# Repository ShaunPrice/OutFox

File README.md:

# OutFox
This is a volunteer project to help save the endangered Bell turtle species. I'm assisting the "Turtles Forever" project team in developing a fox (and dogs) detection and scaring system that uses Artificial Intelligence (AI) to identify the preditors and ward them off. The main preditor causing the damage has been foxes that are not native to Australia and are destroying the turtle nests.

This is the working prototype (PCB not validated) for the solution. It uses MobileNet AI model as it already detects many species of foxes, dogs and wolves.

*Any assistance in this project is welcome!!!*

## Articles About the Project
https://www.abc.net.au/news/2018-03-07/turtle-hatchlings-offer-hope-endangered-bells-turtle/9522182
https://northerntablelands.lls.nsw.gov.au/resource-hub/media-releases/2016/work-begins-on-bells-turtle-recovery-project

Fox and other nuisance animal detection and frightening device. Uses cameras and AI to detect and identify only the nuisance animals.

*This is a Work in Progress*
# Notes for using the Seeed Studio MAIX Bit and the Kendryte K210

## Sipeed MAix BiT for RISC-V AI+IoT
The core of the system is the Sipeed BiT board with camera available from Seeed. 
https://www.seeedstudio.com/Sipeed-MAix-BiT-for-RISC-V-AI-IoT-p-2872.html

This board uses a Kendryte K210 Neural Accellerator for at the edge AI. The board consumes less than 1 Watt of power.

If using this board and camera for night vision using the IR LEDs you'll need to unscrew the lense from the camera and remove the small square IR filter from the back of the lense.

The documentation for this processor is available here:
https://maixpy.sipeed.com/en/

## SiSpeed Downloads
http://dl.sipeed.com/MAIX/
https://github.com/sipeed

## Uploading files and firmware
Use uPyLoader for uploading files and executing script
Use kloader_windows for uploading firmware

The details of obtaining and using these tools is available from the Sipeed website:

https://maixpy.sipeed.com/en/get_started/upload_script.html

## MaixPy Firmware
Builds:   http://dl.sipeed.com/MAIX/MaixPy/release/master/
GitHub: https://github.com/sipeed/MaixPy/releases

## Train, Convert and Run Models for MaixPy 
The following article explains how to train, convert and run AI modules on the MAix BiT and other modules using the Kendryte K210 processor.
https://bbs.sipeed.com/t/topic/682

### Package Kfpkg files
http://blog.sipeed.com/p/390.html
**Note 1:** *SD library does not support long file names.*
**Note 2:** *name.kmodel files are in the zipped file name.kfpkg*

kfpkg files are zipped files containing the following files:

	model.kmodel file that is the inference model
	flash-list.json file that tells the loaded where to put the model in flash memory
	
A typical kfpkg flash-list.json file is below where facedetect.kmodel is the name of the kmodel file:
'''json
{
    "version": "0.1.0",
     "files": [
        {
            "address": 0x00300000,
            "bin": "facedetect.kmodel",
            "sha256Prefix": false
        }
    ]
}
'''

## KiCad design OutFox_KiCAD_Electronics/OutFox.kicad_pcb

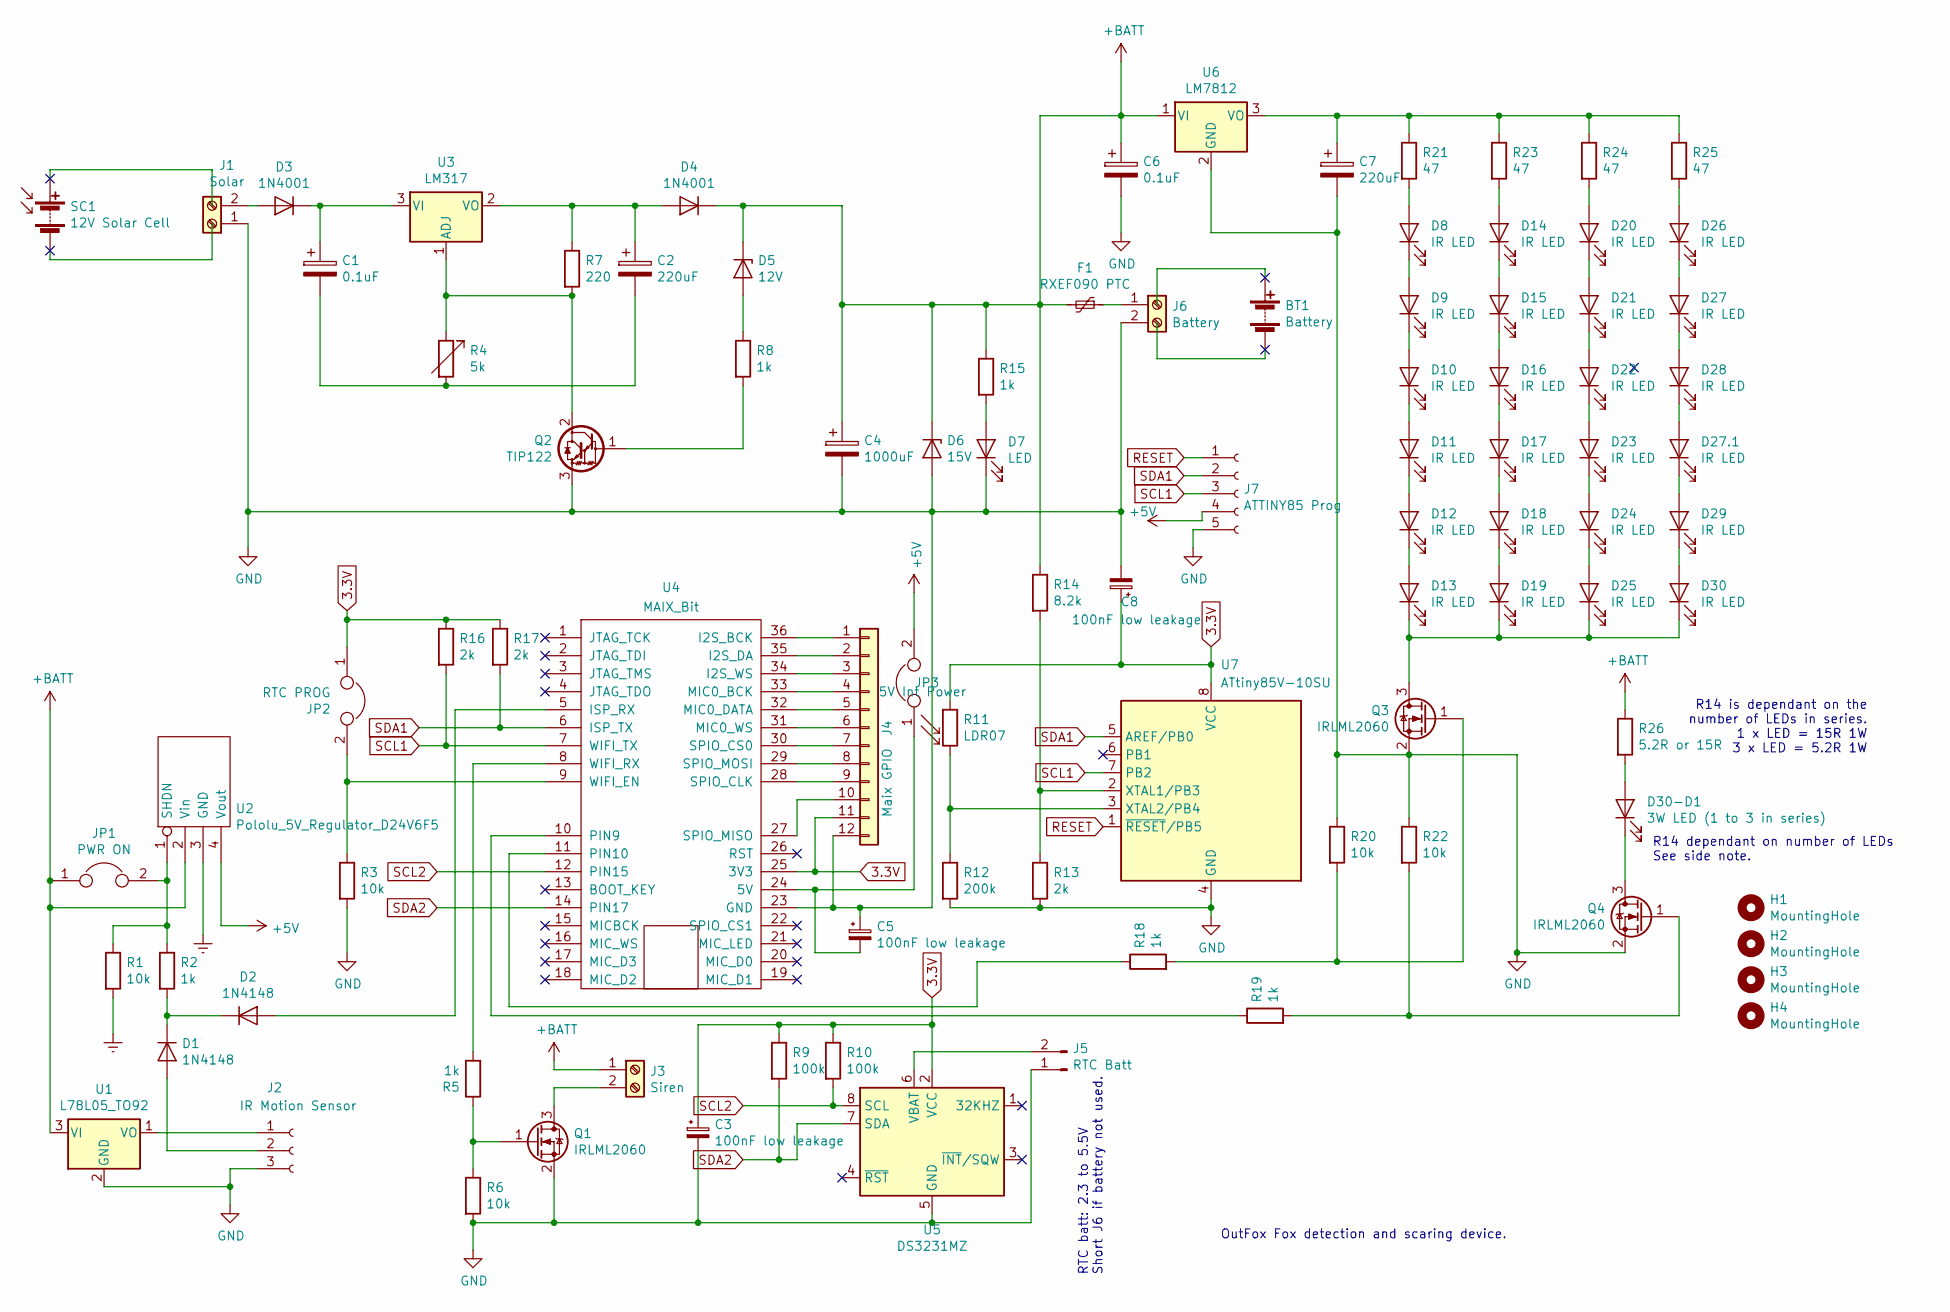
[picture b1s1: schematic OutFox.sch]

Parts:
BT1: Battery
C1, C6: 0.1uF; CP_Radial_D4.0mm_P1.50mm
C2, C7: 220uF; CP_Radial_D5.0mm_P2.50mm
C3, C5, C8: 100nF low leakage; C_0603_HandSoldering
C4: 1000uF; CP_Radial_D5.0mm_P2.50mm
D1, D2: 1N4148; D_A-405_P7.62mm_Horizontal
D3, D4: 1N4001; D_DO-15_P12.70mm_Horizontal
D5: 12V; D_DO-15_P12.70mm_Horizontal
D6: 15V; D_DO-15_P12.70mm_Horizontal
D7: LED; LED_D3.0mm
D8, D9, D10, D11, D12, D13, D14, D15, D16, D17, D18, D19, D20, D21, D22, D23, D24, D25, D26, D27, D27.1, D28, D29, D30: IR LED; LED_D5.0mm
D30-D1: 3W LED (1 to 3 in series); LED_D5.0mm
F1: RXEF090 PTC; Fuse_TE5_Littlefuse-395Series
H1, H2, H3, H4: MountingHole; MountingHole_3.2mm_M3
J1: Solar; TerminalBlock_bornier-2_P5.08mm
J2: IR Motion Sensor; Pin_Header_Straight_1x03_Pitch2.54mm
J3: Siren; TerminalBlock_bornier-2_P5.08mm
J4: Maix GPIO; Socket_Strip_Straight_1x12_Pitch2.54mm
J5: RTC Batt; JST_PH_B2B-PH-K_02x2.00mm_Straight
J6: Battery; TerminalBlock_bornier-2_P5.08mm
J7: ATTINY85 Prog; Pin_Header_Straight_1x05_Pitch2.54mm
JP1: PWR ON; Pin_Header_Straight_1x02_Pitch2.54mm
JP2: RTC PROG; Pin_Header_Straight_1x02_Pitch2.54mm
JP3: 5V Int Power; Pin_Header_Straight_1x02_Pitch2.54mm
Q1, Q3, Q4: IRLML2060; SOT-23
Q2: TIP122; TO-220-3_Vertical
R1, R3, R6, R20, R22: 10k; R_Axial_DIN0207_L6.3mm_D2.5mm_P10.16mm_Horizontal
R2, R5, R8, R15, R18, R19: 1k; R_Axial_DIN0207_L6.3mm_D2.5mm_P10.16mm_Horizontal
R4: 5k; Potentiometer_Trimmer_Bourns_3266Y
R7: 220; R_Axial_DIN0207_L6.3mm_D2.5mm_P10.16mm_Horizontal
R9, R10: 100k; R_0603_HandSoldering
R11: LDR07; R_Axial_DIN0204_L3.6mm_D1.6mm_P2.54mm_Vertical
R12: 200k; R_0603_HandSoldering
R13, R16, R17: 2k; R_0603_HandSoldering
R14: 8.2k; R_0603_HandSoldering
R21, R23, R24, R25: 47; R_Axial_DIN0207_L6.3mm_D2.5mm_P10.16mm_Horizontal
R26: 5.2R or 15R; R_Axial_DIN0207_L6.3mm_D2.5mm_P10.16mm_Horizontal
SC1: 12V Solar Cell
U1: L78L05_TO92; TO-92_Inline_Narrow_Oval
U2: Pololu_5V_Regulator_D24V6F5; Polulu_Voltage_Regulator
U3: LM317; TO-220
U4: MAIX_Bit; MAIXBit
U5: DS3231MZ; SOIC-8_3.9x4.9mm_Pitch1.27mm
U6: LM7812; TO-220-3_Vertical
U7: ATtiny85V-10SU; SOIC-8-N

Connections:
3.3V: C3.1, C8.1, J4.11, JP2.1, R9.1, R10.1, R11.1, R16.1, R17.1, U4.25 (3V3), U5.2 (VCC), U7.8 (VCC)
+5V: J7.4, JP3.2, U2.4 (Vout)
+BATT: C4.1, C6.1, D4.1 (K), D5.1 (K), D6.1 (K), F1.2, J3.1, JP1.1, R14.1, R15.1, R26.1, U1.3 (VI), U2.2 (Vin), U6.1 (VI)
Earth: R1.2, U2.3 (GND)
GND: C3.2, C4.2, C5.1, C6.2, C7.2, C8.2, D6.2 (A), D7.1 (K), J1.1, J2.3 (GND), J4.12, J5.1, J6.2, J7.5, Q1.2 (S), Q2.3 (E), Q3.2 (S), Q4.2 (S), R3.2, R6.2, R12.2, R13.2, R20.1, R22.1, U1.2 (GND), U4.23 (GND), U5.5 (GND), U6.2 (GND), U7.4 (GND)
unnamed: C1.1, D3.1 (K), U3.3 (VI)
unnamed: C1.2, C2.2, R4.2
unnamed: C2.1, D4.2 (A), R7.1, U3.2 (VO)
unnamed: C5.2, JP3.1, U4.24 (5V)
unnamed: C7.1, R21.1, R23.1, R24.1, R25.1, U6.3 (VO)
unnamed: D1.1 (K), D2.1 (K), R2.2
unnamed: D1.2 (A), J2.2 (OUT)
unnamed: D2.2 (A), U4.5 (ISP_RX)
unnamed: D3.2 (A), J1.2
unnamed: D5.2 (A), R8.1
unnamed: D7.2 (A), R15.2
unnamed: D8.1 (K), D9.2 (A)
unnamed: D8.2 (A), R21.2
unnamed: D10.1 (K), D11.2 (A)
unnamed: D9.1 (K), D10.2 (A)
unnamed: D11.1 (K), D12.2 (A)
unnamed: D12.1 (K), D13.2 (A)
unnamed: D13.1 (K), D19.1 (K), D25.1 (K), D30.1 (K), Q3.3 (D)
unnamed: D14.1 (K), D15.2 (A)
unnamed: D14.2 (A), R23.2
unnamed: D15.1 (K), D16.2 (A)
unnamed: D16.1 (K), D17.2 (A)
unnamed: D17.1 (K), D18.2 (A)
unnamed: D18.1 (K), D19.2 (A)
unnamed: D20.1 (K), D21.2 (A)
unnamed: D20.2 (A), R24.2
unnamed: D21.1 (K), D22.2 (A)
unnamed: D22.1 (K), D23.2 (A)
unnamed: D23.1 (K), D24.2 (A)
unnamed: D24.1 (K), D25.2 (A)
unnamed: D26.1 (K), D27.2 (A)
unnamed: D26.2 (A), R25.2
unnamed: D27.1 (K), D28.2 (A)
unnamed: D27.1.1 (K), D29.2 (A)
unnamed: D27.1.2 (A), D28.1 (K)
unnamed: D29.1 (K), D30.2 (A)
unnamed: D30-D1.1 (K), Q4.3 (D)
unnamed: D30-D1.2 (A), R26.2
unnamed: F1.1, J6.1
unnamed: J2.1 (5V), U1.1 (VO)
unnamed: J3.2, Q1.3 (D)
unnamed: J4.1, U4.36 (I2S_BCK)
unnamed: J4.2, U4.35 (I2S_DA)
unnamed: J4.3, U4.34 (I2S_WS)
unnamed: J4.4, U4.33 (MIC0_BCK)
unnamed: J4.5, U4.32 (MIC0_DATA)
unnamed: J4.6, U4.31 (MIC0_WS)
unnamed: J4.7, U4.30 (SPIO_CS0)
unnamed: J4.8, U4.29 (SPIO_MOSI)
unnamed: J4.9, U4.28 (SPIO_CLK)
unnamed: J4.10, U4.27 (SPIO_MISO)
unnamed: J5.2, U5.6 (VBAT)
unnamed: JP1.2, R1.1, R2.1, U2.1 (SHDN)
unnamed: JP2.2, R3.1, U4.9 (WIFI_EN)
unnamed: Q1.1 (G), R5.1, R6.1
unnamed: Q2.1 (B), R8.2
unnamed: Q2.2 (C), R4.1, R7.2, U3.1 (ADJ)
unnamed: Q3.1 (G), R18.2, R20.2
unnamed: Q4.1 (G), R19.2, R22.2
unnamed: R5.2, U4.8 (WIFI_RX)
unnamed: R11.2, R12.1, U7.3 (XTAL2/PB4)
unnamed: R13.1, R14.2, U7.2 (XTAL1/PB3)
unnamed: R18.1, U4.11 (PIN10)
unnamed: R19.1, U4.10 (PIN9)
RESET: J7.1, U7.1 (~RESET~/PB5)
SCL1: J7.3, R16.2, U4.7 (WIFI_TX), U7.7 (PB2)
SCL2: R10.2, U4.12 (PIN15), U5.8 (SCL)
SDA1: J7.2, R17.2, U4.6 (ISP_TX), U7.5 (AREF/PB0)
SDA2: R9.2, U4.14 (PIN17), U5.7 (SDA)

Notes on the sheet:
R14 is dependant on the number of LEDs in series. 1 x LED = 15R 1W 3 x LED = 5.2R 1W
R14 dependant on number of LEDs See side note.
RTC batt: 2.3 to 5.5V Short J6 if battery not used.
OutFox Fox detection and scaring device.

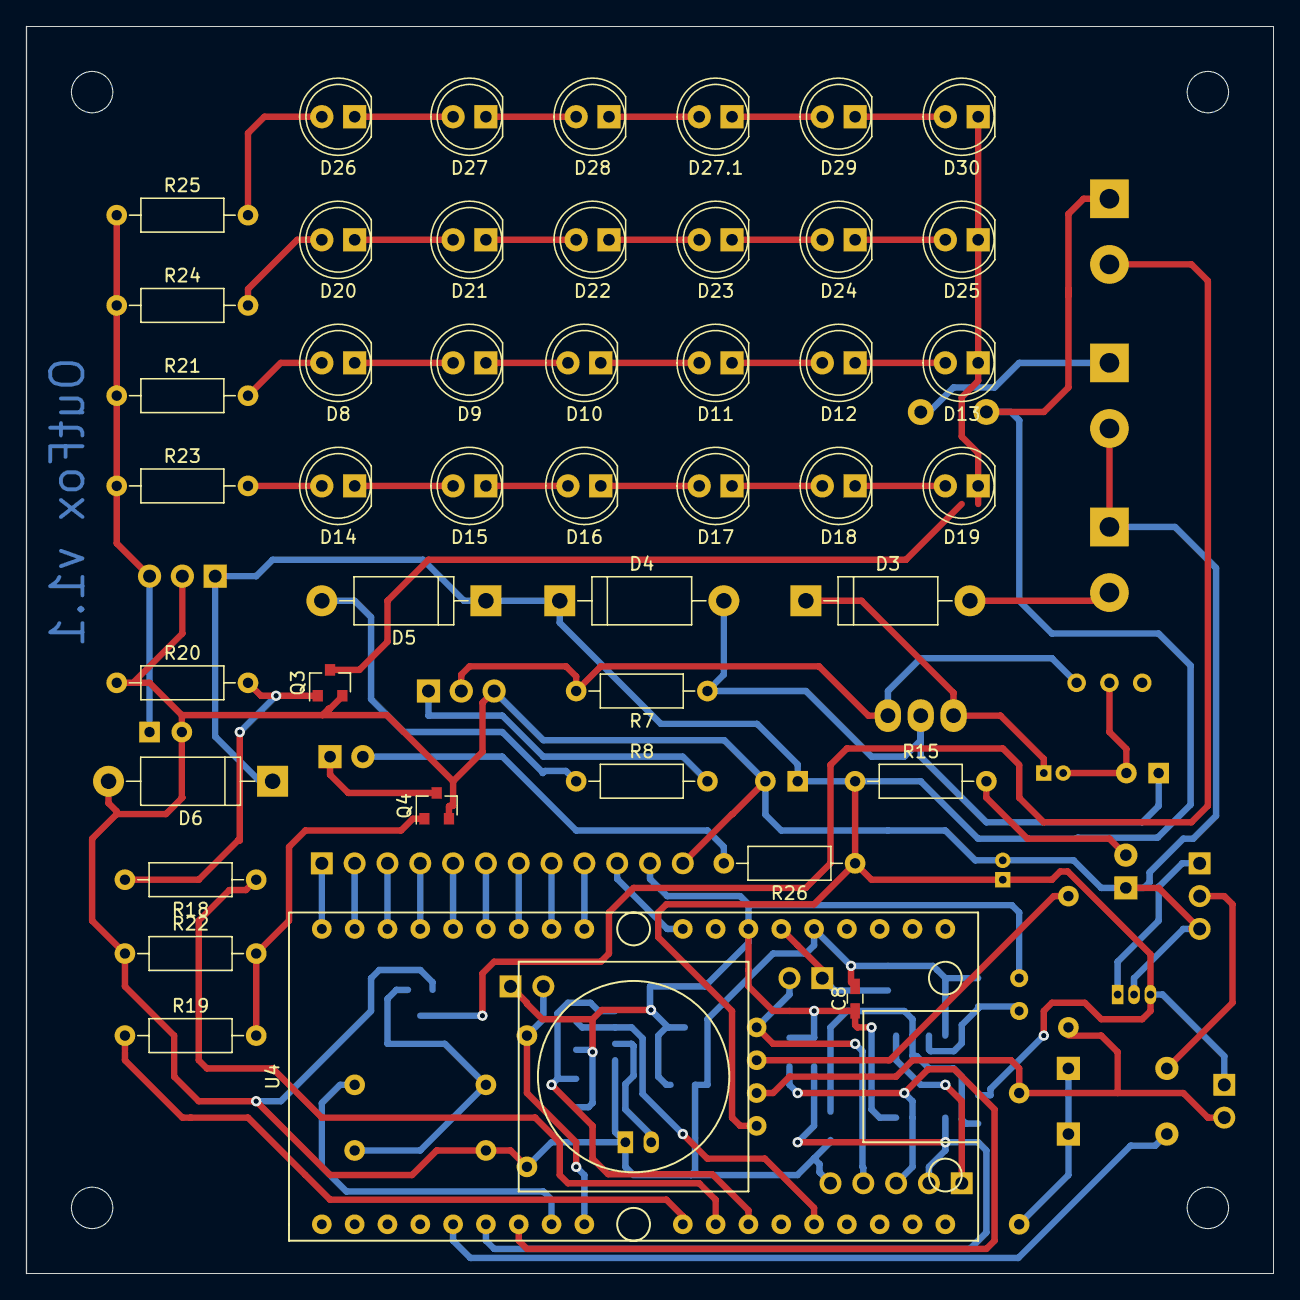
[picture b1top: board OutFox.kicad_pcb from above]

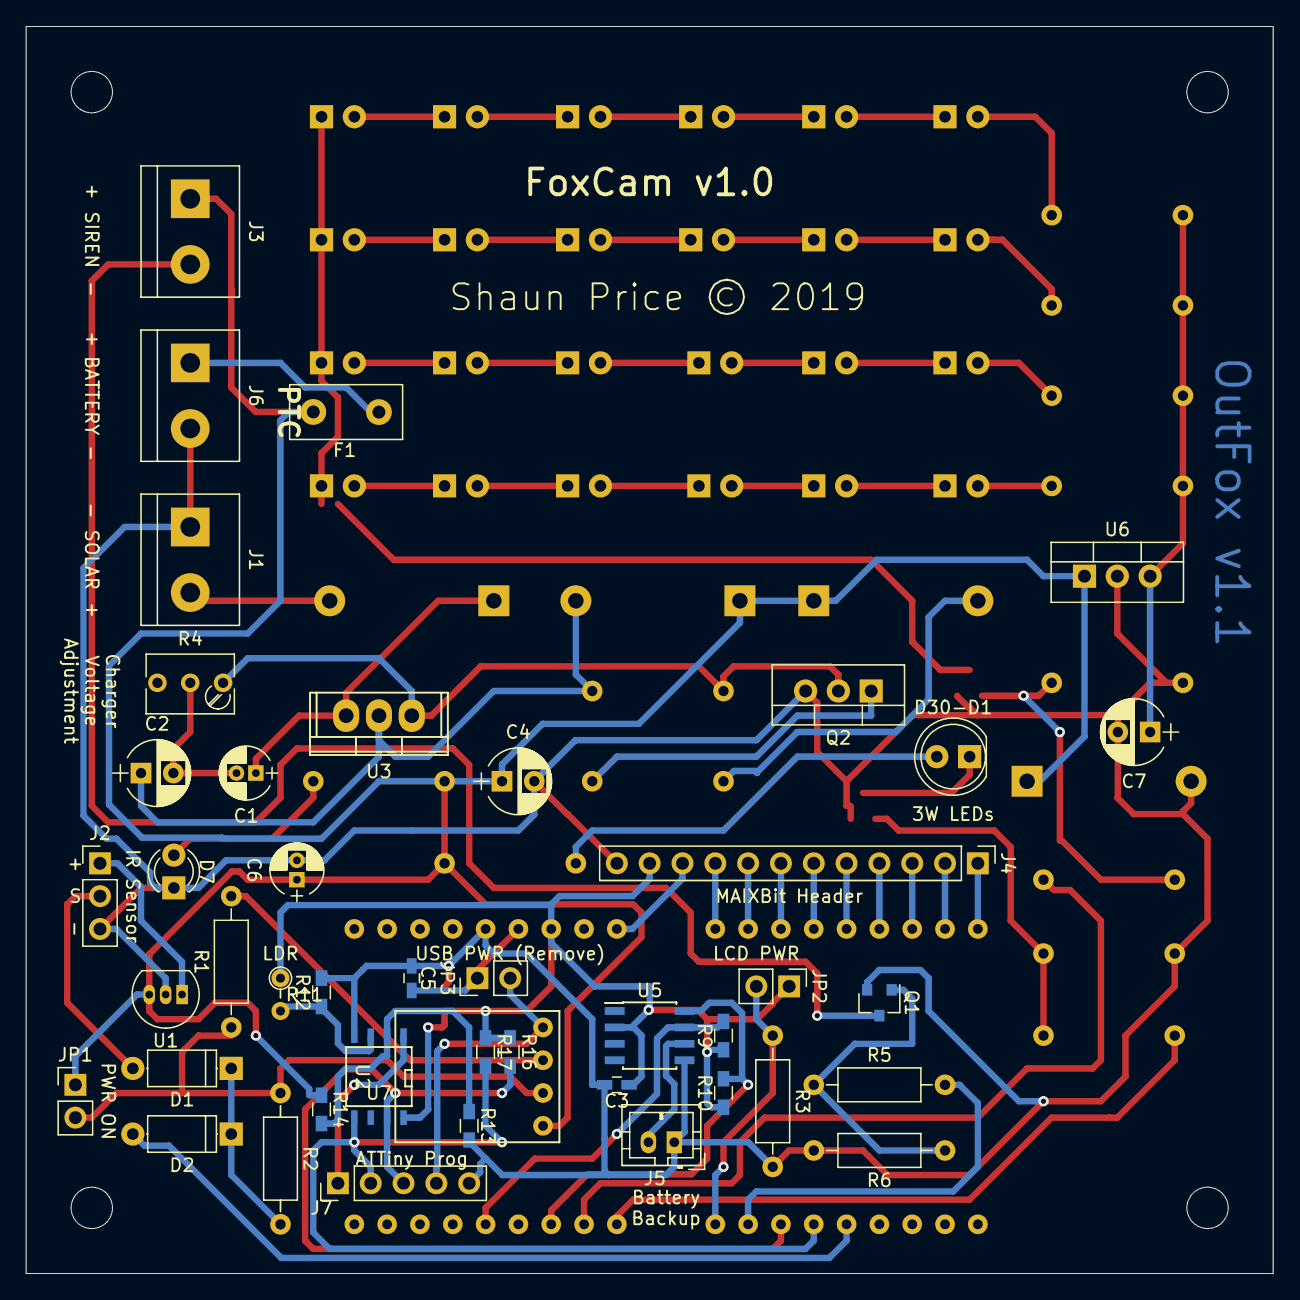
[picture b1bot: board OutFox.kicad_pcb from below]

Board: 2 copper layers, 96.5 x 96.5 mm, 92 parts (44 on the bottom side), 74 nets.

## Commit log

2019-10-27 Models upload and read.me updates
    Uploaded mobilnet models used and read.me file updates. The models are converted for the MAix BiT.
2019-10-27 KiCAD schematics and PCB files
    Added the KiCAD electronic schematics and PCB files.
    Note that the design has not been validated at this stage.

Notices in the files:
OutFox_KiCAD_Electronics/OutFox.kicad_pcb:
Shaun Price © 2019
